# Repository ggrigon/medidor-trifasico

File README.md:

# Medidor de Tensão Trifásico - ESP32 + PZEM-004T

Medidor trifásico DIY para monitoramento de sistema 220/380V em tempo real. Lê tensão, corrente, potência, energia, frequência e fator de potência das 3 fases com interface web, display OLED, histórico em SD card e integração MQTT.

**Custo estimado:** ~R$ 350-430 (vs R$ 900+ de soluções comerciais como Shelly Pro 3EM)

**Landing page:** [ggrigon.github.io/medidor-trifasico](https://ggrigon.github.io/medidor-trifasico/)

## Funcionalidades

- **Leitura das 3 fases:** tensão, corrente, potência, energia, frequência, fator de potência
- **Display OLED:** 5 páginas auto-rotativas (overview + detalhe de cada fase + alarmes)
- **Dashboard Web:** interface responsiva com gráficos em tempo real via WebSocket
- **Histórico SD Card:** log CSV diário (~1.5 MB/dia), cartão de 32GB = ~58 anos
- **MQTT:** integração com Home Assistant, Grafana (via Telegraf + InfluxDB)
- **Alarmes:** sobretensão (>253V) e subtensão (<197V) com buzzer, LED e notificação web
- **OTA:** atualização de firmware via Wi-Fi

## Lista de Materiais

| # | Componente | Qtd | Função |
|---|---|---|---|
| 1 | ESP32 DevKit V1 (30 pinos, CP2102) | 1 | Microcontrolador principal - WiFi + Bluetooth |
| 2 | PZEM-004T v3.0 com TC split-core 100A | 3 | Medidor de energia por fase (Modbus RTU) |
| 3 | Display OLED SSD1306 128x64 I2C | 1 | Display local para leituras |
| 4 | Módulo SD Card SPI | 1 | Armazenamento de histórico CSV |
| 5 | Cartão microSD (4GB+ classe 10) | 1 | Mídia de armazenamento |
| 6 | Buzzer passivo 5V (BP18) | 1 | Alarme sonoro |
| 7 | Placa perfurada dupla face | 1 | Montagem dos componentes |
| 8 | Fios jumper Dupont (M-M, M-F) | ~40 | Conexões entre componentes |
| 9 | Resistor 4.7k 1/4W | 2 | Pull-up I2C (SDA/SCL) |
| 10 | Resistor 330R 1/4W | 1 | Limitador LED status |
| 11 | Capacitor eletrolítico 100uF 16V | 1 | Desacoplamento 5V |
| 12 | Capacitor cerâmico 100nF 50V | 1 | Filtro 3.3V |
| 13 | LED verde 3mm | 1 | Indicador de status |
| 14 | Borne KRE 2 vias | 1-6 | Conexões parafusadas |
| 15 | Barras de pinos macho/fêmea | 3 | Soquetes e conectores |
| 16 | Fonte 5V 1A (USB ou HLK-PM01) | 1 | Alimentação do ESP32 |

> **IMPORTANTE:** Os PZEMs devem ter CT tipo **split-core** (aberto, tipo grampo). NÃO comprar com CT fechado (closed loop). Ver detalhes completos em [`LISTA_MATERIAIS.md`](LISTA_MATERIAIS.md).

## Pinagem

```
ESP32 GPIO16 (RX2) ──bus──> 3x PZEM TX   (Modbus RTU, addr 0x01/0x02/0x03)
ESP32 GPIO17 (TX2) ──bus──> 3x PZEM RX
ESP32 GPIO21 (SDA) ──────> OLED SDA      (pull-up 4.7k para 3.3V)
ESP32 GPIO22 (SCL) ──────> OLED SCL      (pull-up 4.7k para 3.3V)
ESP32 GPIO23 (MOSI) ─────> SD MOSI
ESP32 GPIO19 (MISO) ─────> SD MISO
ESP32 GPIO18 (SCK) ──────> SD SCK
ESP32 GPIO5  (CS) ───────> SD CS
ESP32 GPIO4  ────────────> Buzzer passivo
ESP32 GPIO2  ── R 330R ──> LED verde
```

Ver esquemático completo em [`hardware/schematic.pdf`](hardware/schematic.pdf) ou [`hardware/schematic.txt`](hardware/schematic.txt).

## Estrutura do Projeto

```
medidor-trifasico/
├── platformio.ini              # Configuração PlatformIO
├── partitions.csv              # Tabela de partições customizada (1.87MB app + 2.06MB LittleFS)
├── LISTA_MATERIAIS.md          # Lista detalhada com preços e links de compra (BR)
├── STATUS.md                   # Andamento do projeto
├── src/
│   ├── main.cpp                # Setup/loop, orquestração cooperativa com millis()
│   ├── config.h                # Pinos, constantes, structs (PhaseData, MeterData)
│   ├── pzem_reader.h/.cpp      # Leitura dos 3 PZEMs via Modbus RTU
│   ├── display_manager.h/.cpp  # OLED SSD1306 (5 páginas rotativas)
│   ├── web_server.h/.cpp       # AsyncWebServer + WebSocket (tempo real)
│   ├── mqtt_client.h/.cpp      # Publicação MQTT (Home Assistant / Grafana)
│   ├── sd_logger.h/.cpp        # Log CSV no SD card (rotação diária)
│   ├── alarm_manager.h/.cpp    # Alarmes sub/sobretensão com buzzer
│   ├── wifi_manager.h/.cpp     # WiFi STA + fallback AP
│   ├── ntp_time.h/.cpp         # Sincronização NTP
│   └── ota_manager.h/.cpp      # Atualização OTA via Wi-Fi
├── data/                        # LittleFS -> dashboard web
│   ├── index.html
│   ├── style.css
│   ├── app.js
│   └── chart.min.js.gz
├── hardware/                    # Projeto PCB KiCad 7 (90x80mm, 2 camadas)
│   ├── medidor-trifasico.kicad_pro
│   ├── medidor-trifasico.kicad_sch
│   ├── medidor-trifasico.kicad_pcb
│   ├── schematic.pdf
│   └── schematic.txt
└── tools/
    └── set_pzem_addresses.cpp   # Utilitário config endereços PZEM
```

## Instalação

### Pré-requisitos
- [PlatformIO CLI](https://platformio.org/install/cli) ou PlatformIO IDE (VS Code)
- Cabo USB-C para o ESP32

### 1. Configurar endereços dos PZEMs

Cada PZEM precisa de um endereço Modbus único. De fábrica, todos vêm com 0xF8. Configure um por vez:

```bash
# Conecte apenas 1 PZEM ao ESP32
# Edite tools/set_pzem_addresses.cpp -> TARGET_ADDRESS = 0x01 (L1)
pio run -e set_pzem_addr -t upload
pio device monitor
# Repita para 0x02 (L2) e 0x03 (L3)
```

### 2. Configurar WiFi e MQTT

Edite `src/config.h`:
```cpp
#define WIFI_SSID       "SuaRedeWiFi"
#define WIFI_PASSWORD   "SuaSenha"
#define MQTT_SERVER     "192.168.1.100"
```

### 3. Compilar e fazer upload

```bash
# Firmware
pio run -e esp32 -t upload

# Filesystem (dashboard web)
pio run -e esp32 -t uploadfs
```

### 4. Verificar

```bash
# Monitor serial
pio device monitor

# Acesse o dashboard web pelo IP mostrado no OLED/serial
```

## Dashboard Web

Acesse `http://IP_DO_ESP32` no navegador. O dashboard mostra:
- 3 cards com leituras de cada fase em tempo real
- Gráfico de potência dos últimos 5 minutos
- Barra de alarme quando há sub/sobretensão

## Integração MQTT

Topics publicados:
```
medidor/L1/voltage    medidor/L2/voltage    medidor/L3/voltage
medidor/L1/current    medidor/L2/current    medidor/L3/current
medidor/L1/power      medidor/L2/power      medidor/L3/power
medidor/L1/energy     medidor/L2/energy     medidor/L3/energy
medidor/L1/frequency  medidor/L2/frequency  medidor/L3/frequency
medidor/L1/pf         medidor/L2/pf         medidor/L3/pf
medidor/data          (JSON completo)
medidor/status        (online/offline - LWT)
medidor/alarm         (alertas com retain)
```

## PCB Customizada (opcional)

Projeto KiCad 7 pronto em `hardware/` para fabricação na JLCPCB:
- PCB carrier board 90x80mm, 2 camadas
- Todos os módulos encaixam via pin header (ESP32, PZEMs, OLED, SD, buzzer)
- Resistores e capacitores em SMD 0805
- Plano de terra em ambas as camadas
- Furos de montagem M3 nos 4 cantos

## Segurança

Os módulos PZEM-004T conectam-se a tensão de rede (220/380V). A instalação **deve ser feita por alguém confortável com eletricidade de rede**, dentro de um gabinete apropriado com espaçamento adequado. Sempre desligue a energia antes de fazer conexões. Os CTs split-core podem ser instalados com a rede energizada, mas tome cuidado com os fios de tensão do PZEM.

## Licença

Este projeto é de uso pessoal/hobby. Use por sua conta e risco.

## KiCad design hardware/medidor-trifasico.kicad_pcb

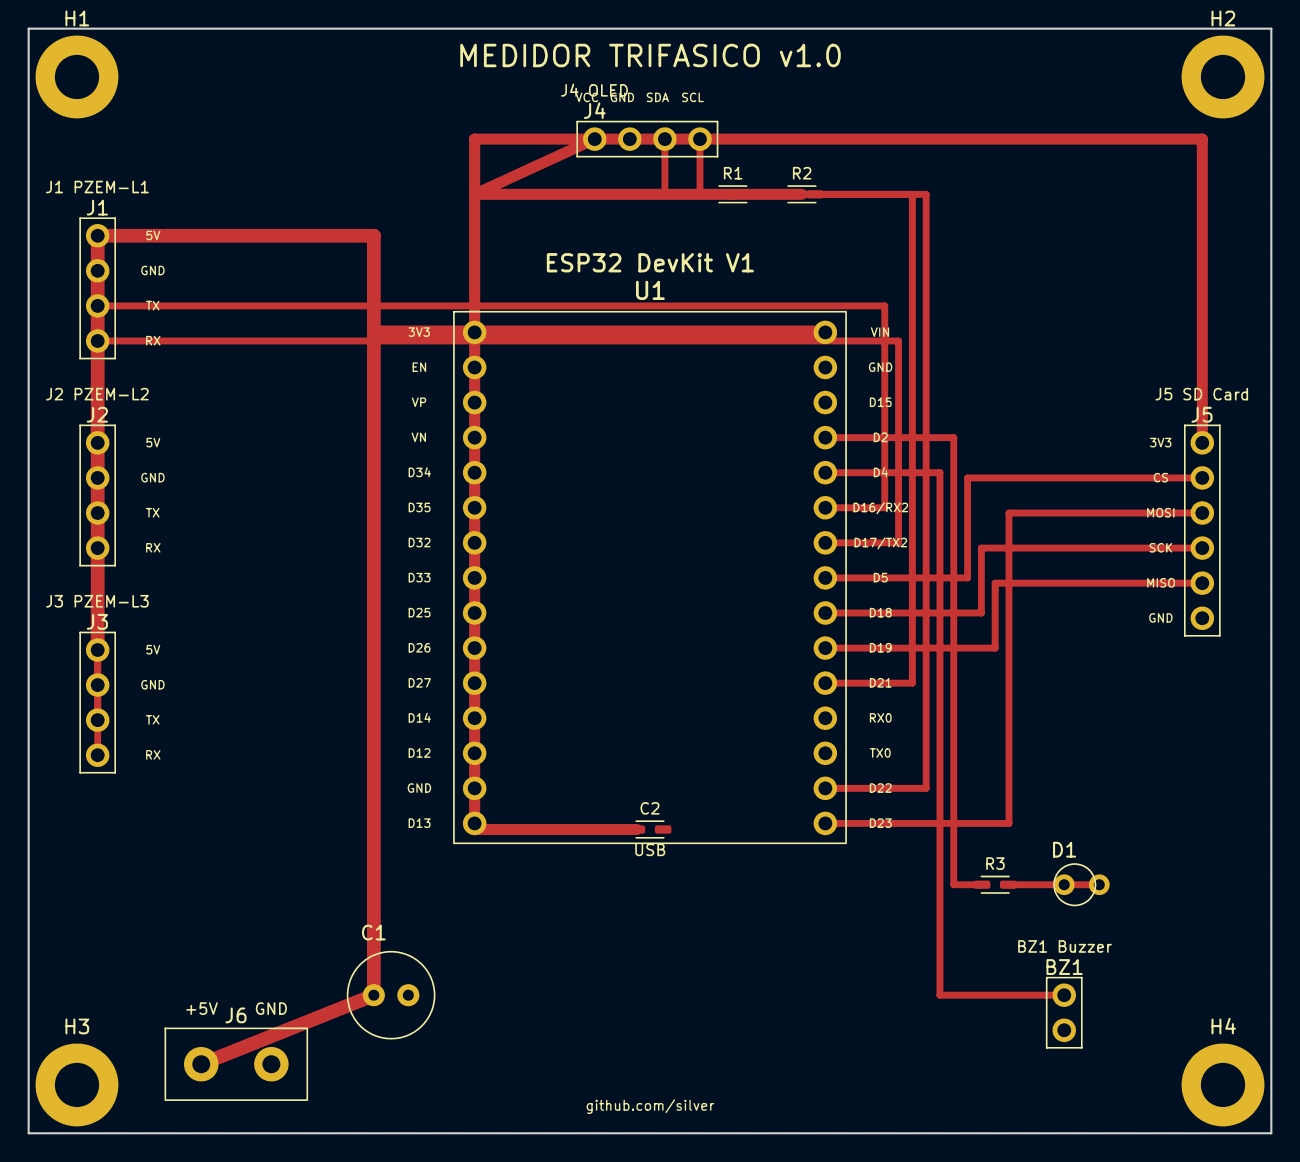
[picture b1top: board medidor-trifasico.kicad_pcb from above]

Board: 2 copper layers, 90.0 x 80.0 mm, 18 parts (0 on the bottom side), 14 nets.

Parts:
BZ1: Buzzer; Connector_PinHeader_1x02_P2.54mm_Vertical
C1: 100uF; CP_Radial_D6.3mm_P2.50mm
C2: 100nF; R_0805_2012Metric
D1: LED_Green; LED_D3.0mm
H1, H2, H3, H4: MountingHole_M3; MountingHole_3.2mm_M3
J1: PZEM-L1; Connector_PinHeader_1x04_P2.54mm_Vertical
J2: PZEM-L2; Connector_PinHeader_1x04_P2.54mm_Vertical
J3: PZEM-L3; Connector_PinHeader_1x04_P2.54mm_Vertical
J4: OLED; Connector_PinHeader_1x04_P2.54mm_Vertical
J5: SD_Card; Connector_PinHeader_1x06_P2.54mm_Vertical
J6: 5V_IN; TerminalBlock_bornier-2_P5.08mm
R1, R2: 4.7k; R_0805_2012Metric
R3: 330R; R_0805_2012Metric
U1: ESP32_DevKit_V1

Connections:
+3V3: C2.1, J4.1, J5.1, R1.1, R2.1, U1.1
+5V: C1.1, J1.1, J2.1, J3.1, J6.1, U1.16
BUZZER: BZ1.1, U1.20
GND: BZ1.2, C1.2, C2.2, D1.1, J1.2, J2.2, J3.2, J4.2, J5.6, J6.2, U1.14, U1.17
LED_OUT: R3.1, U1.19
LED_R: D1.2, R3.2
PZEM_RX: J1.4, J2.4, J3.4, U1.22
PZEM_TX: J1.3, J2.3, J3.3, U1.21
SCL: J4.4, R2.2, U1.29
SDA: J4.3, R1.2, U1.26
SD_CS: J5.2, U1.23
SD_MISO: J5.5, U1.25
SD_MOSI: J5.3, U1.30
SD_SCK: J5.4, U1.24

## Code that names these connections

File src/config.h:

#pragma once

#include <Arduino.h>

// --- Pinos PZEM (Serial2) ---
#define PZEM_RX_PIN    16
#define PZEM_TX_PIN    17

// --- Pinos OLED (I2C) ---
#define OLED_SDA       21
#define OLED_SCL       22
#define OLED_WIDTH     128
#define OLED_HEIGHT    64
#define OLED_ADDR      0x3C

// --- Pinos SD Card (SPI) ---
#define SD_CS_PIN       5
#define SD_MOSI_PIN    23
#define SD_MISO_PIN    19
#define SD_SCK_PIN     18

// --- Buzzer e LED ---
#define BUZZER_PIN      4
#define LED_PIN         2

// --- Enderecos Modbus PZEM ---
#define PZEM_ADDR_L1   0x01
#define PZEM_ADDR_L2   0x02
#define PZEM_ADDR_L3   0x03

// --- WiFi ---
#define WIFI_SSID       "SEU_SSID"
#define WIFI_PASSWORD   "SUA_SENHA"
#define AP_SSID         "Medidor-Config"
#define AP_PASSWORD     "12345678"
#define WIFI_TIMEOUT_MS 15000

// --- MQTT ---
#define MQTT_SERVER     "192.168.1.100"
#define MQTT_PORT       1883
#define MQTT_USER       ""
#define MQTT_PASSWORD   ""
#define MQTT_CLIENT_ID  "medidor-trifasico"
#define MQTT_TOPIC_BASE "medidor"

// --- NTP ---
#define NTP_SERVER      "pool.ntp.org"
#define NTP_GMT_OFFSET  -10800  // BRT = UTC-3
#define NTP_DST_OFFSET  0

// --- Intervalos (ms) ---
#define INTERVAL_PZEM       1000
#define INTERVAL_DISPLAY     500
#define INTERVAL_WEBSOCKET  1000
#define INTERVAL_SD_LOG    10000
#define INTERVAL_MQTT       5000
#define INTERVAL_ALARM      1000
#define INTERVAL_WIFI      30000
#define INTERVAL_NTP     3600000

// --- Display ---
#define DISPLAY_PAGE_INTERVAL 5000
#define DISPLAY_NUM_PAGES     5

// --- Alarmes ---
#define ALARM_OVERVOLTAGE   253.0f  // +15% de 220V
#define ALARM_UNDERVOLTAGE  197.0f  // -10% de 220V
#define ALARM_DEBOUNCE_ON       3   // leituras consecutivas para ativar
#define ALARM_DEBOUNCE_OFF      5   // leituras consecutivas para desativar

// --- SD Logger ---
#define SD_LOG_DIR      "/logs"

// --- Estruturas de dados ---
struct PhaseData {
    float voltage    = 0;
    float current    = 0;
    float power      = 0;
    float energy     = 0;
    float frequency  = 0;
    float powerFactor = 0;
    bool valid       = false;
};

struct MeterData {
    PhaseData phase[3];
    unsigned long timestamp = 0;
    String isoTime;
};

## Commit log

2026-02-21 Implementacao completa do medidor trifasico ESP32 + PZEM-004T
    - 3x PZEM-004T v3.0 via Modbus RTU (Serial2)
    - Display OLED SSD1306 com 5 paginas auto-rotativas
    - Dashboard web responsivo com WebSocket e graficos Chart.js
    - Log CSV diario no SD card
    - MQTT com topics individuais e agregado (compativel Home Assistant/Grafana)
    - Alarmes de sub/sobretensao com debounce, buzzer e notificacao web
2026-02-21 Adiciona projeto KiCad PCB e atualiza lista de materiais com precos BR
    - Cria projeto KiCad 7 completo (esquematico + PCB 90x80mm 2 camadas)
    - PCB carrier board para ESP32 DevKit + 3x PZEM-004T + OLED + SD Card
    - Exporta PDF do esquematico e diagrama ASCII de referencia
    - Atualiza LISTA_MATERIAIS.md com precos em R$ (fev/2026)
    - Adiciona links diretos: Usinainfo, Mercado Livre, AliExpress
    - Destaca necessidade de CT split-core (aberto) no PZEM-004T
2026-02-21 Atualiza lista de materiais com links diretos Usinainfo para todos os itens
    Pesquisa completa no site da Usinainfo com codigos, precos PIX e links
    diretos para cada produto. Elimina referencias vagas a "balcao". Adiciona
    opcoes de caixa Patola, tabela detalhada de custo (R$183 Usinainfo +
    PZEM ML/AliExpress), e nota sobre cap 100nF indisponivel.
2026-02-21 Corrige links quebrados da Usinainfo (formato SEO-friendly)
    URLs no formato antigo index.php?route=product/product redirecionavam
    para homepage. Atualiza todos os 9 links para formato SEO novo.
    Corrige precos: ESP32 R$66,36, OLED R$25,46, SD R$7,89, Buzzer R$6,94.
    Subtotal Usinainfo atualizado: R$189,86.
2026-02-21 Adiciona STATUS.md com andamento completo do projeto
    Inclui status do firmware, hardware/PCB, lista de compras com codigos
    e precos confirmados, proximos passos em 4 fases e limitacoes conhecidas.
2026-02-21 Atualiza README com precos BR, estrutura completa e links para docs
    Precos em reais (R$310-390), tabela de materiais com nota sobre CT
    split-core, pinagem com pull-ups e resistores, estrutura atualizada
    com ota_manager e hardware/, secao sobre PCB KiCad, e referencia
    aos arquivos LISTA_MATERIAIS.md e STATUS.md.
2026-02-21 Adiciona landing page GitHub Pages (docs/index.html)
    Site vitrine one-page com: seção motivação (DIY vs Shelly), galeria de 5 dashboards,
    diagrama SVG com zoom, BOM atualizada 2026, toggle PT/EN + dark/light mode.
2026-02-21 Atualiza contributors
2026-02-21 Corrige acentos em português e atualiza preços nos .md
    Adiciona acentuação correta (trifásico, tensão, potência, frequência,
    integração, módulo, etc.) nos 3 arquivos markdown. Atualiza preço de
    referência para R$350-430 vs R$900+ Shelly Pro 3EM.
